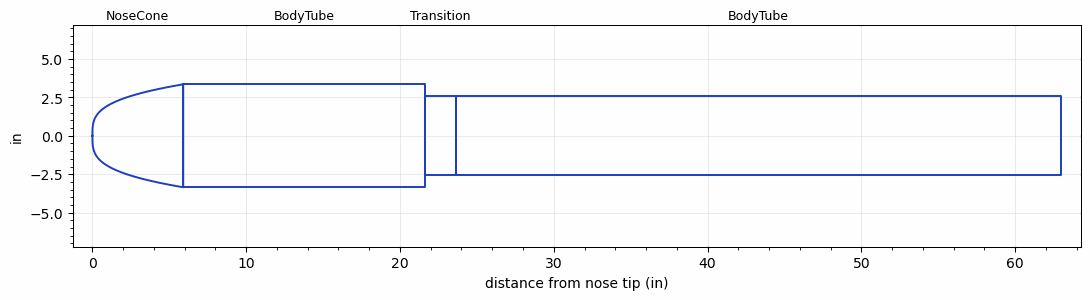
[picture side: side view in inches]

<RASAeroDocument>
 <FileVersion>2</FileVersion>
 <RocketDesign>
  <NoseCone>
   <Length>5.9056</Length>
   <Diameter>6.693</Diameter>
   <Shape>Power Law</Shape>
   <Location>0</Location>
   <PowerLaw>0.3</PowerLaw>
  </NoseCone>
  <BodyTube>
   <Length>15.748</Length>
   <Diameter>6.693</Diameter>
   <Location>5.9056</Location>
  </BodyTube>
  <Transition>
   <Length>1.9685</Length>
   <Diameter>5.1182</Diameter>
   <Location>21.6536</Location>
   <RearDiameter>5.1182</RearDiameter>
  </Transition>
  <BodyTube>
   <Length>39.37</Length>
   <Diameter>5.1182</Diameter>
   <Location>23.6221</Location>
  </BodyTube>
  <Surface>Smooth (Zero Roughness)</Surface>
  <ModifiedBarrowman>False</ModifiedBarrowman>
  <Turbulence>False</Turbulence>
  <UseBooster1>False</UseBooster1>
  <UseBooster2>False</UseBooster2>
 </RocketDesign>
 <LaunchSite>
  <Altitude>0</Altitude>
  <Pressure>0</Pressure>
  <RodAngle>0</RodAngle>
  <RodLength>4</RodLength>
  <Temperature>74</Temperature>
  <WindSpeed>0</WindSpeed>
 </LaunchSite>
 <Recovery>
  <Altitude1>1000</Altitude1>
  <Altitude2>1000</Altitude2>
  <DeviceType1>None</DeviceType1>
  <DeviceType2>None</DeviceType2>
  <Event1>False</Event1>
  <Event2>False</Event2>
  <Size1>1</Size1>
  <Size2>1</Size2>
  <EventType1>None</EventType1>
  <EventType2>None</EventType2>
  <CD1>1.33</CD1>
  <CD2>1.33</CD2>
 </Recovery>
</RASAeroDocument>
